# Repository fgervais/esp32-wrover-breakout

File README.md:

# Objective

The goal of this project is to make a lower cost esp32 module than the TinyPICO
for my other projects.

The TinyPICO is great. It is small and uses low current in deep sleep but it
costs me about 40$ CAD once it reaches me. I'd prefer if I could have something
at around 10$ CAD which is the goal of this project.

# Breadboard Version

## Price

The bare PCB costs 2.67$ CAD from OSH Park.
Digikey BOM cost for 1 unit is 8.09$ CAD.

Total is 10.76$ CAD (worst case)

## PCB

[OSH Park](https://oshpark.com/shared_projects/hciJOsgc)

## BOM

[Digikey BOM](https://www.digikey.ca/BOM/Create/CreateSharedBom?bomId=8507784)

## Programming

The programming is done through the JST connector using the 
[Adafruit 3309](https://www.adafruit.com/product/3309) along
with the following adapter:

- [Github](https://github.com/fgervais/project-adafruit-3309-adapter/tree/master/hardware/jst-zh)
- [OSH Park](https://oshpark.com/shared_projects/B9to99oI)

### Firmware

The GENERIC-SPIRAM firmware can be downloaded from the following page:

https://micropython.org/download/esp32/

The module has been validated to work with:

esp32spiram-idf4-20210202-v1.14.bin

# M.2 Version

## Price

Bare PCB (OSH Park): 3.47$ CAD
BOM (Digikey, 1 unit): 7.84$ CAD

Total: 11.31$ CAD (worst case)

## BOM

[Digikey BOM](https://www.digikey.ca/BOM/Create/CreateSharedBom?bomId=8549197)

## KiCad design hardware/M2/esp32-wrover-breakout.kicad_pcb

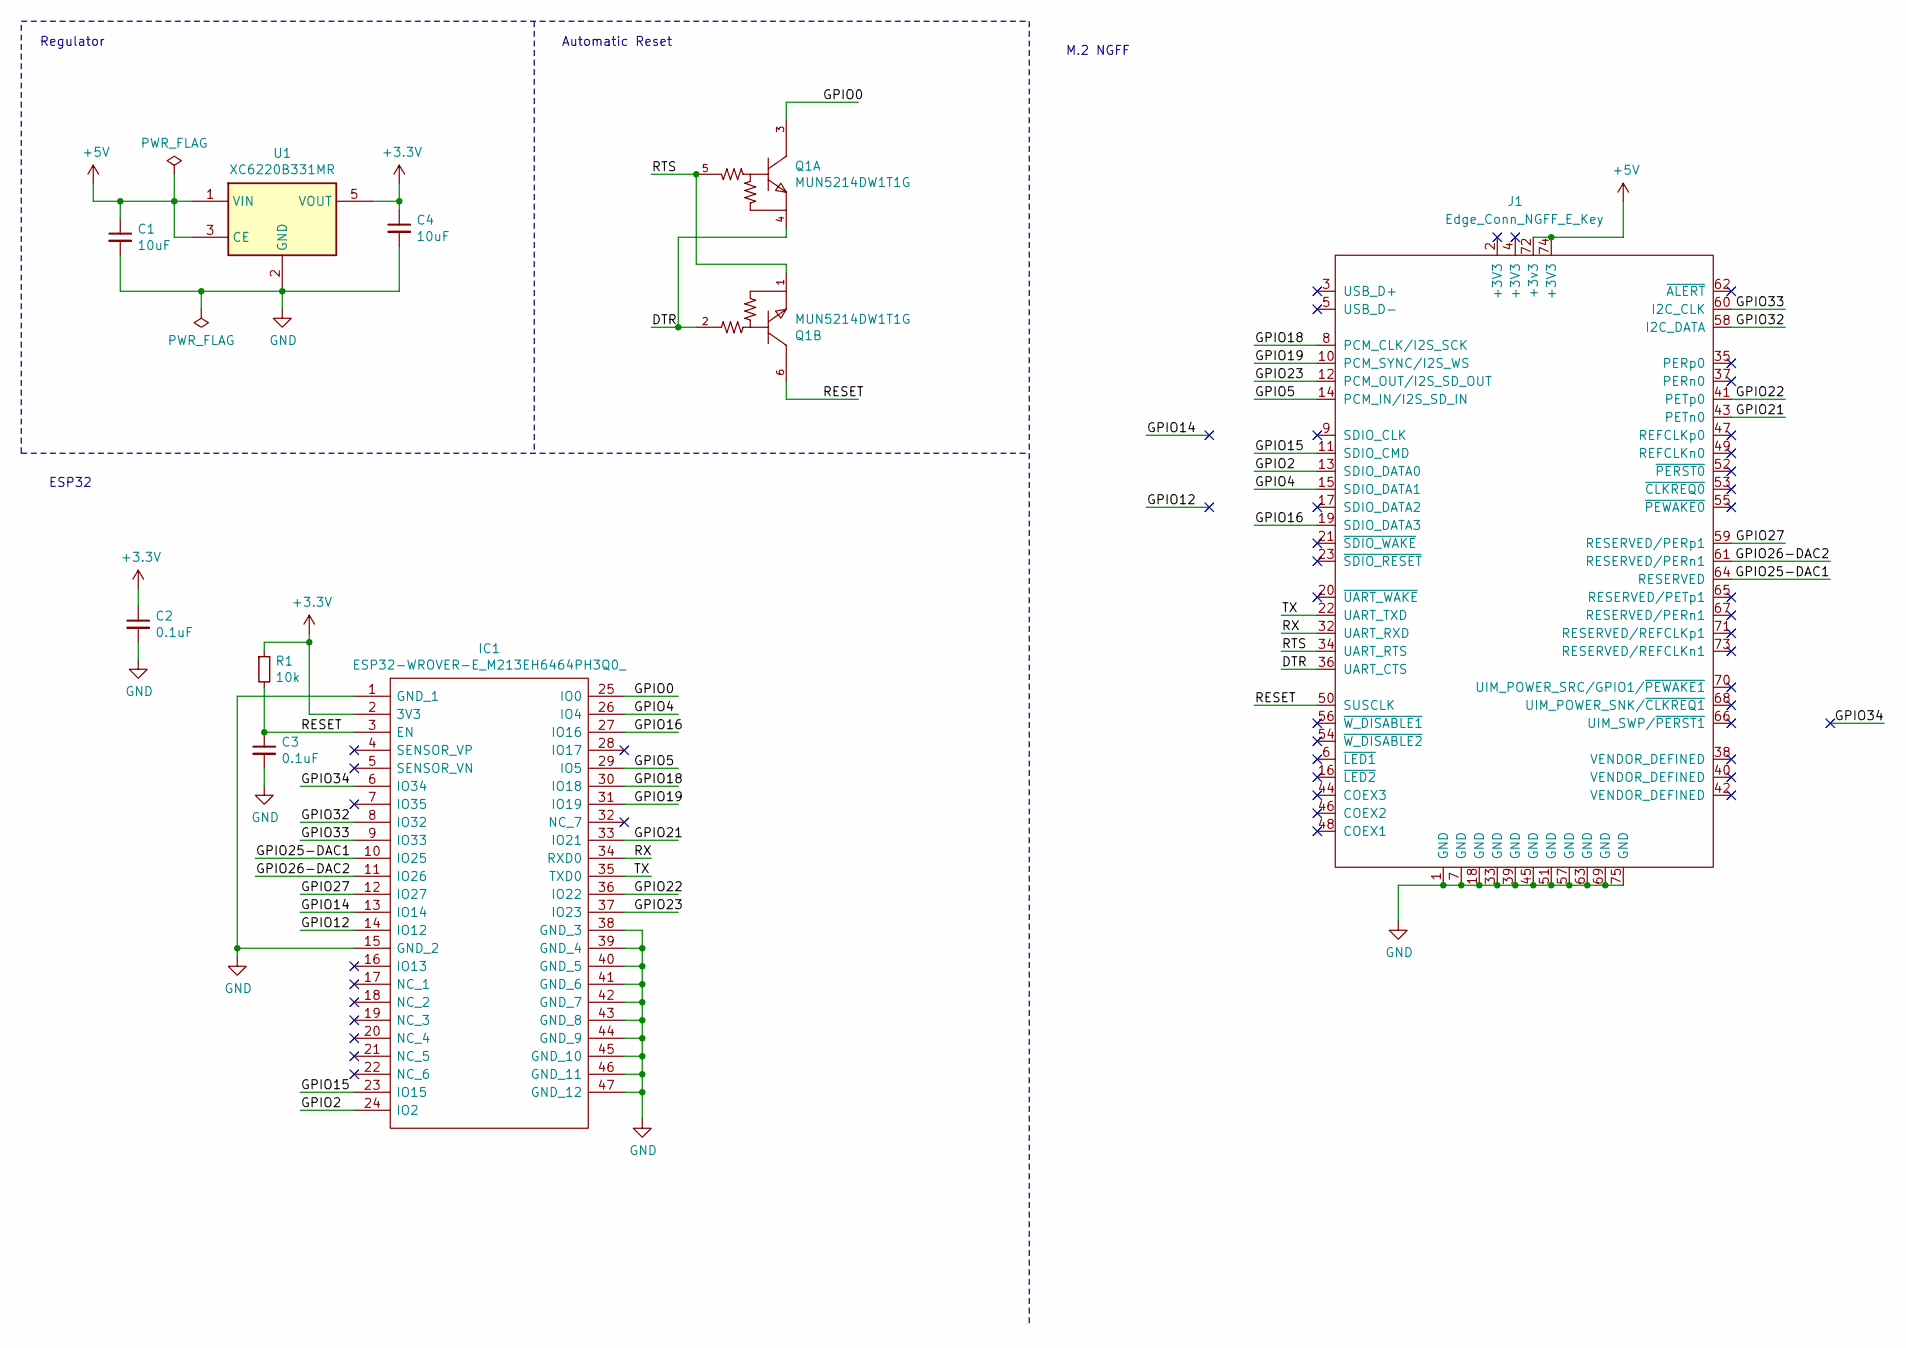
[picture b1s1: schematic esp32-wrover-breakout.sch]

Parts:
C1, C4: 10uF; C_0805_2012Metric_Pad1.18x1.45mm_HandSolder
C2, C3: 0.1uF; C_0603_1608Metric_Pad1.08x0.95mm_HandSolder
IC1: ESP32-WROVER-E_M213EH6464PH3Q0_; ESP32WROVEREM213EH6464PH3Q0; Manufacturer_Part_Number ESP32-WROVER-E(M213EH6464PH3Q0); Mouser Part Number 356-ESP32WRVE26464PC
J1: Edge_Conn_NGFF_E_Key; NGFF_E
Q1: MUN5214DW1T1G; On_Semiconductor-MUN5214DW1T1G-Manufacturer_Recommended
R1: 10k; R_0603_1608Metric_Pad0.98x0.95mm_HandSolder
U1: XC6220B331MR; SOT-23-5

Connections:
+3V3: C2.1, C4.1, IC1.2 (3V3), R1.1, U1.5 (VOUT)
+5V: C1.1, J1.72 (+3v3), J1.74 (+3V3), U1.1 (VIN), U1.3 (CE)
/DTR: J1.36 (UART_CTS), Q1.2 (B), Q1.4 (E)
/GPIO0: IC1.25 (IO0), Q1.3 (C)
/GPIO2: IC1.24 (IO2), J1.13 (SDIO_DATA0)
/GPIO4: IC1.26 (IO4), J1.15 (SDIO_DATA1)
/GPIO5: IC1.29 (IO5), J1.14 (PCM_IN/I2S_SD_IN)
/GPIO12: IC1.14 (IO12)
/GPIO14: IC1.13 (IO14)
/GPIO15: IC1.23 (IO15), J1.11 (SDIO_CMD)
/GPIO16: IC1.27 (IO16), J1.19 (SDIO_DATA3)
/GPIO18: IC1.30 (IO18), J1.8 (PCM_CLK/I2S_SCK)
/GPIO19: IC1.31 (IO19), J1.10 (PCM_SYNC/I2S_WS)
/GPIO21: IC1.33 (IO21), J1.43 (PETn0)
/GPIO22: IC1.36 (IO22), J1.41 (PETp0)
/GPIO23: IC1.37 (IO23), J1.12 (PCM_OUT/I2S_SD_OUT)
/GPIO25-DAC1: IC1.10 (IO25), J1.64 (RESERVED)
/GPIO26-DAC2: IC1.11 (IO26), J1.61 (RESERVED/PERn1)
/GPIO27: IC1.12 (IO27), J1.59 (RESERVED/PERp1)
/GPIO32: IC1.8 (IO32), J1.58 (I2C_DATA)
/GPIO33: IC1.9 (IO33), J1.60 (I2C_CLK)
/GPIO34: IC1.6 (IO34)
/RESET: C3.1, IC1.3 (EN), J1.50 (SUSCLK), Q1.6 (C), R1.2
/RTS: J1.34 (UART_RTS), Q1.1 (E), Q1.5 (B)
/RX: IC1.34 (RXD0), J1.32 (UART_RXD)
/TX: IC1.35 (TXD0), J1.22 (UART_TXD)
GND: C1.2, C2.2, C3.2, C4.2, IC1.1 (GND_1), IC1.15 (GND_2), IC1.38 (GND_3), IC1.39 (GND_4), IC1.40 (GND_5), IC1.41 (GND_6), IC1.42 (GND_7), IC1.43 (GND_8), IC1.44 (GND_9), IC1.45 (GND_10), IC1.46 (GND_11), IC1.47 (GND_12), J1.1 (GND), J1.7 (GND), J1.18 (GND), J1.33 (GND), J1.39 (GND), J1.45 (GND), J1.51 (GND), J1.57 (GND), J1.63 (GND), J1.69 (GND), J1.75 (GND), U1.2 (GND)

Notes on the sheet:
Automatic Reset
Regulator
M.2 NGFF
ESP32

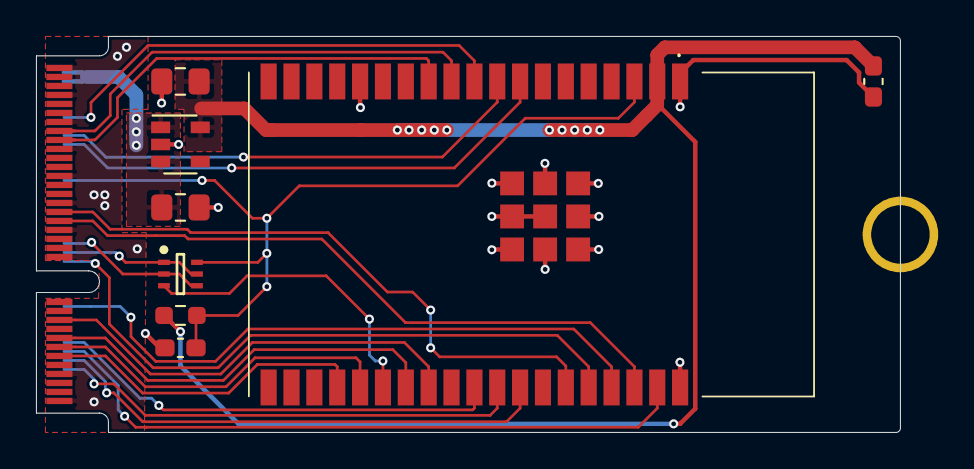
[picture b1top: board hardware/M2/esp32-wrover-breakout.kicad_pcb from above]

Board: 2 copper layers, 48.0 x 22.0 mm, 9 parts (0 on the bottom side), 24 nets.

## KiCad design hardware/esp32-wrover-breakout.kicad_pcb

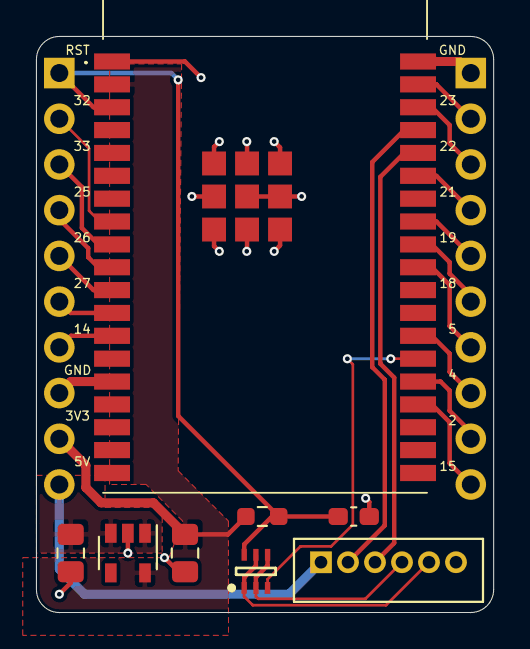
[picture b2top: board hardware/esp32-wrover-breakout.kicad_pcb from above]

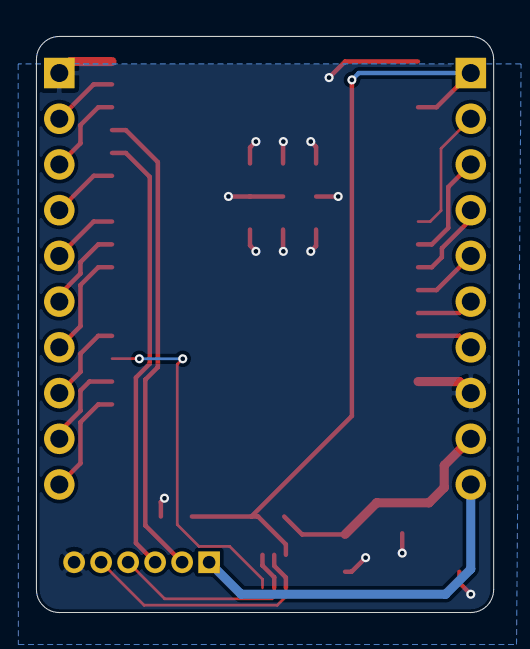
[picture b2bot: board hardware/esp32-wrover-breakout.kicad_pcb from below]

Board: 2 copper layers, 25.4 x 32.0 mm, 10 parts (2 on the bottom side), 24 nets.

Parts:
C1, C4: 10uF; C_0805_2012Metric_Pad1.18x1.45mm_HandSolder
C3: 0.1uF; C_0603_1608Metric_Pad1.08x0.95mm_HandSolder
IC1: ESP32-WROVER-E_M213EH6464PH3Q0_; ESP32WROVEREM213EH6464PH3Q0
J1: Conn_01x06_Male; JST_B6B-ZR(LF)(SN)
J2, J3: Conn_01x10_Male; PinHeader_1x10_P2.54mm_Vertical
Q1: MUN5214DW1T1G; On_Semiconductor-MUN5214DW1T1G-Manufacturer_Recommended
R1: 10k; R_0603_1608Metric_Pad0.98x0.95mm_HandSolder
U1: XC6220B331MR; SOT-23-5

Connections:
+3V3: C4.1, IC1.2, J2.9, R1.1, U1.5
+5V: C1.1, J1.1, J2.10, U1.1, U1.3
/DTR: J1.4, Q1.2, Q1.4
/GPIO0: IC1.25, Q1.3
/GPIO2: IC1.24, J3.9
/GPIO4: IC1.26, J3.8
/GPIO5: IC1.29, J3.7
/GPIO14: IC1.13, J2.7
/GPIO15: IC1.23, J3.10
/GPIO18: IC1.30, J3.6
/GPIO19: IC1.31, J3.5
/GPIO21: IC1.33, J3.4
/GPIO22: IC1.36, J3.3
/GPIO23: IC1.37, J3.2
/GPIO25: IC1.10, J2.4
/GPIO26: IC1.11, J2.5
/GPIO27: IC1.12, J2.6
/GPIO32: IC1.8, J2.2
/GPIO33: IC1.9, J2.3
/RESET: C3.1, IC1.3, J2.1, Q1.6, R1.2
/RTS: J1.5, Q1.1, Q1.5
/RX: IC1.34, J1.3
/TX: IC1.35, J1.2
GND: C1.2, C3.2, C4.2, IC1.1, IC1.15, IC1.38, IC1.39, IC1.40, IC1.41, IC1.42, IC1.43, IC1.44, IC1.45, IC1.46, IC1.47, J1.6, J2.8, J3.1, U1.2

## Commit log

2020-12-26 Blank project with ESP module in schematic
2020-12-27 Schematic ready
2020-12-28 PCB placement and silkscreen done
2020-12-29 First routing done
2020-12-29 Rev 1.0
2021-01-10 Add an M.2 design cloned from the breadboard one
2021-01-12 M.2 schematic + first placement
2021-01-14 First M.2 routing
2021-01-14 Rotate the screw pad
2021-01-14 Remove a little piece of track
2021-01-14 A couple finishing touches
2021-01-17 Print
2021-01-17 Add M.2 spec
2021-01-19 Fix forgotten no-connect
2021-01-19 Fix mounting hole size
    Allow for the 3mm bushing.
2021-01-27 First README version
2021-01-28 Add populated board image
2021-01-29 Print the breadboard version
2021-01-29 Use the picture on the breadboard
2021-02-11 Add version of previous commit
2021-02-14 Add M.2 version
2021-02-14 Add pricing details
2021-02-14 Typos
2021-02-16 Add the BOM of the breadboard version
2021-02-16 README formatting
2021-02-16 Add M.2 BOM
2021-02-19 Add a link to the OSH Park board
2021-02-27 Add programming section
2021-04-06 Change the mounting hole size
